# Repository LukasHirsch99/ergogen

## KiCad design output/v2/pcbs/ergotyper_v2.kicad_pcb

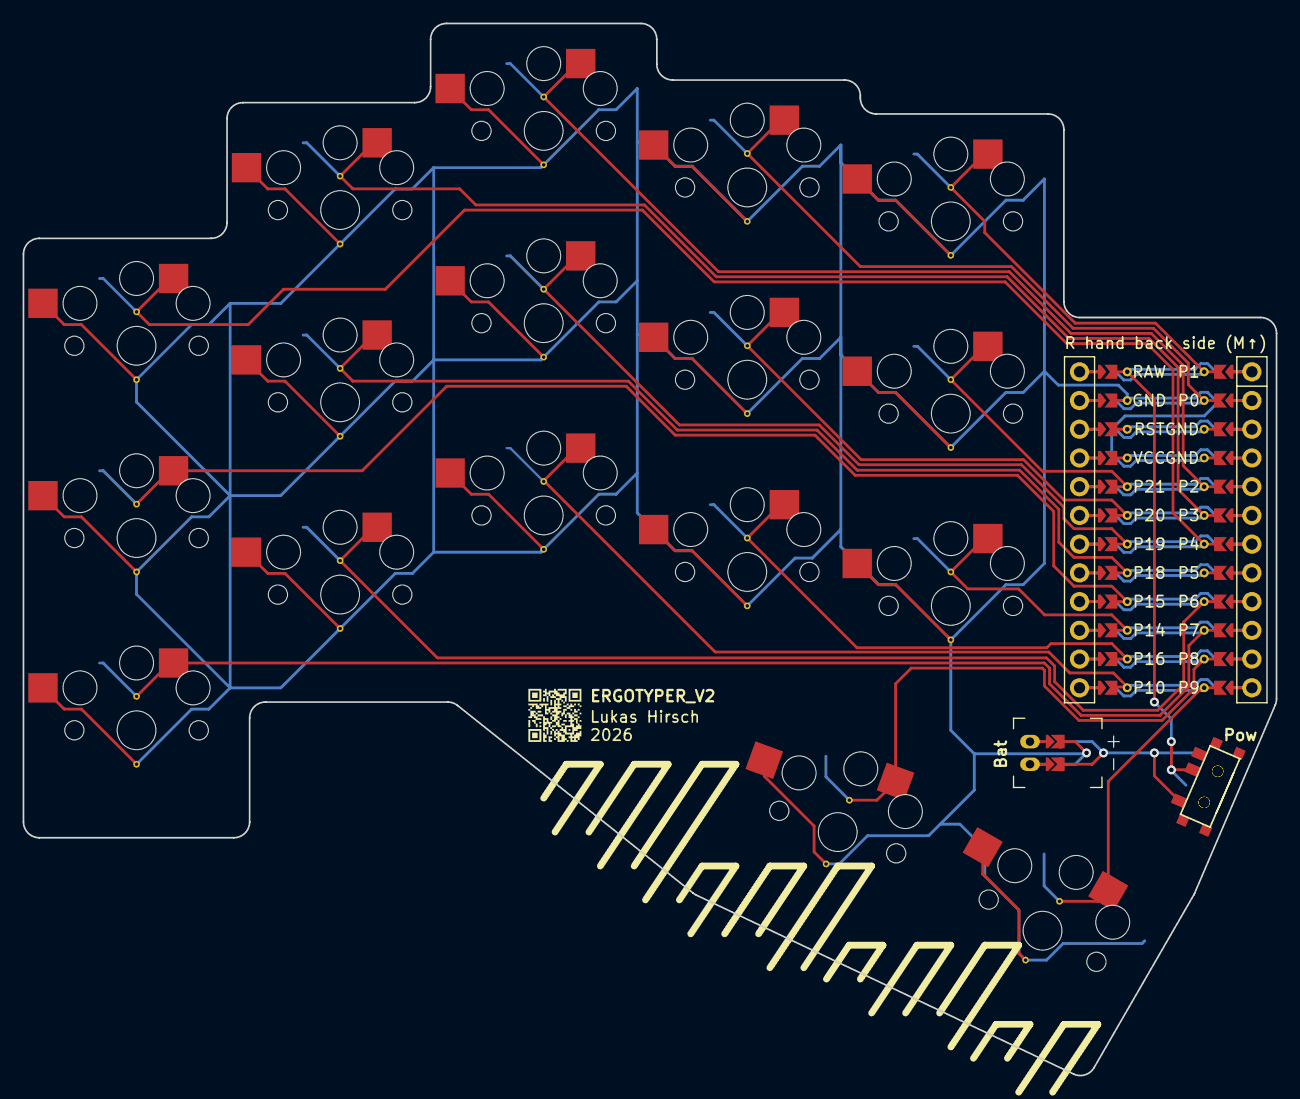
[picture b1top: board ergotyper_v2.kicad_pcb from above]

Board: 2 copper layers, 110.8 x 93.0 mm, 21 parts (0 on the bottom side), 22 nets.

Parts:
JST1: battery_connector_jst_ph_2
MCU1: mcu_nice_nano
S1, S2, S3, S4, S5, S6, S7, S8, S9, S10, S11, S12, S13, S14, S15, S16, S17: PG1350
T1, T2: SPDT_C128955

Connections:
BAT_P: JST1.1, T1.1, T2.1
GND: JST1.2, MCU1.103, MCU1.104, MCU1.123, S1.2, S2.2, S3.2, S4.2, S5.2, S6.2, S7.2, S8.2, S9.2, S10.2, S11.2, S12.2, S13.2, S14.2, S15.2, S16.2, S17.2
JST1_1: JST1.11, JST1.21, JST1.31
JST1_2: JST1.12, JST1.22, JST1.32
P0: MCU1.102, S12.1
P1: MCU1.101, S15.1
P2: MCU1.105, S9.1
P3: MCU1.106, S6.1
P4: MCU1.107, S3.1
P6: MCU1.109, S4.1
P7: MCU1.110, S1.1
P8: MCU1.111, S16.1
P9: MCU1.112, S17.1
P10: MCU1.113, S7.1
P14: MCU1.115, S13.1
P15: MCU1.116, S2.1
P16: MCU1.114, S10.1
P18: MCU1.117, S5.1
P19: MCU1.118, S8.1
P20: MCU1.119, S11.1
P21: MCU1.120, S14.1
RAW: MCU1.124, T1.2, T2.2

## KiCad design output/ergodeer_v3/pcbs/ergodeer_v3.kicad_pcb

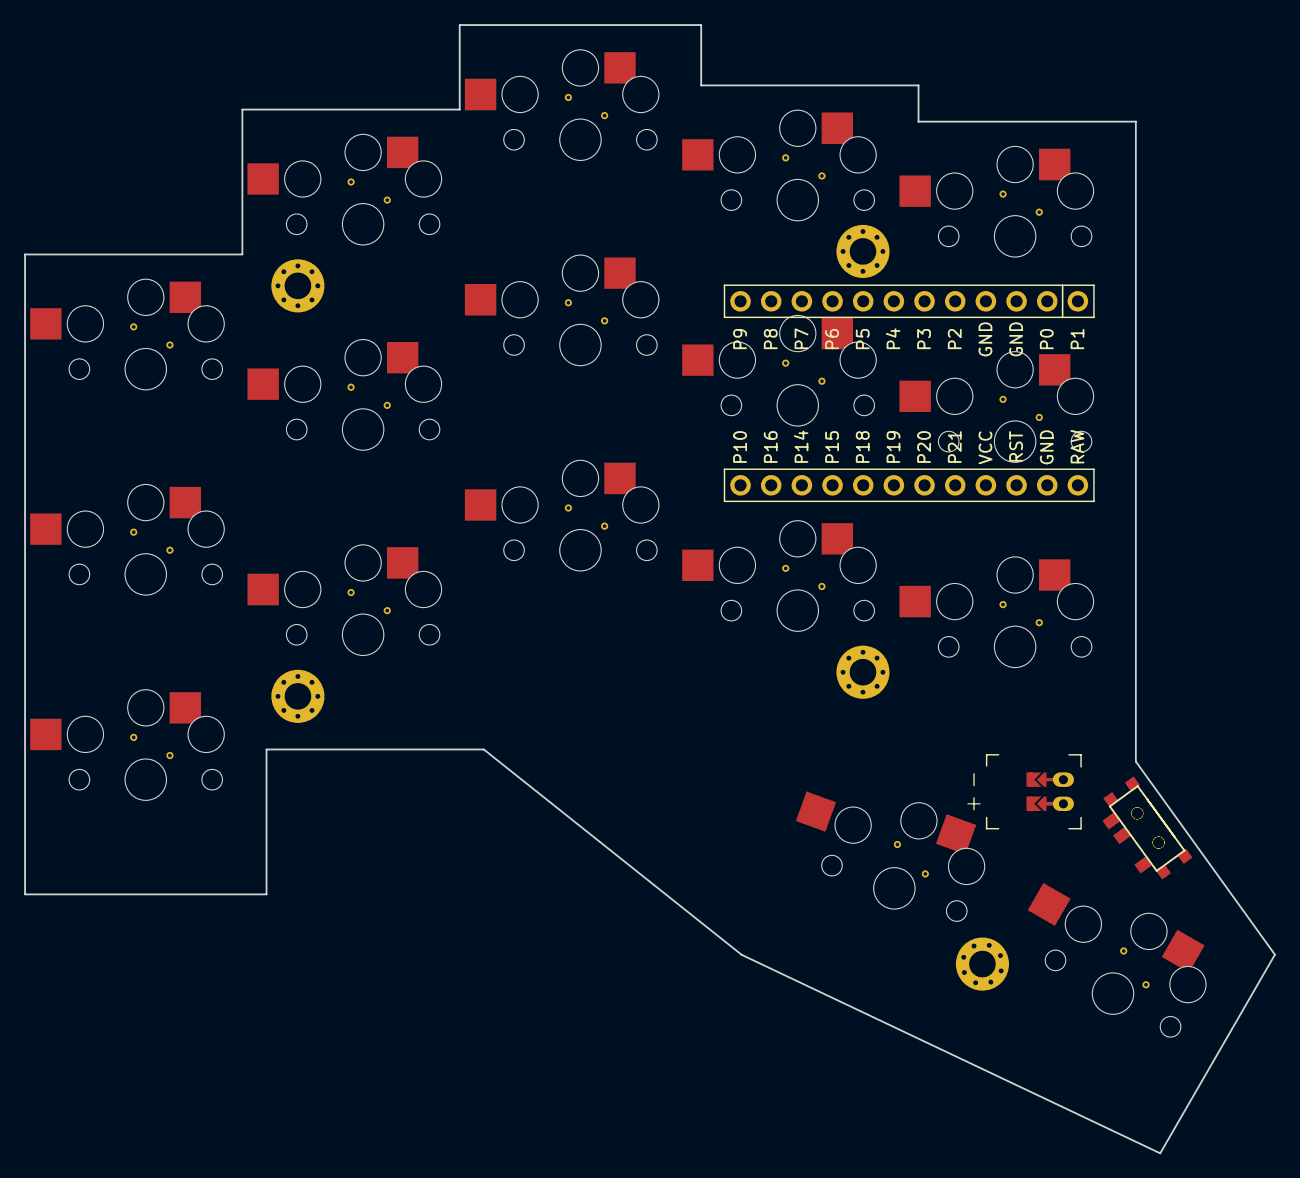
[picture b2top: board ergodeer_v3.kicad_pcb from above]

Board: 2 copper layers, 103.5 x 93.4 mm, 26 parts (0 on the bottom side), 22 nets.

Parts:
JST1: battery_connector_jst_ph_2
MCU1: mcu_nice_nano
S1, S2, S3, S4, S5, S6, S7, S8, S9, S10, S11, S12, S13, S14, S15, S16, S17: PG1350
T1, T2: SPDT_C128955
_35, _36, _37, _38, _39: MountingHole_2.2mm_M2_Pad_Via

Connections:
BAT_P: JST1.1, T1.1, T2.1
GND: JST1.2, MCU1.2, MCU1.21, MCU1.22, S1.2, S2.2, S3.2, S4.2, S5.2, S6.2, S7.2, S8.2, S9.2, S10.2, S11.2, S12.2, S13.2, S14.2, S15.2, S16.2, S17.2
JST1_1: JST1.11, JST1.21, JST1.31
JST1_2: JST1.12, JST1.22, JST1.32
P0: MCU1.23, S14.1
P1: MCU1.24, S15.1
P2: MCU1.20, S12.1
P3: MCU1.19, S9.1
P4: MCU1.18, S6.1
P5: MCU1.17, S3.1
P6: MCU1.16, S11.1
P7: MCU1.15, S8.1
P8: MCU1.14, S5.1
P10: MCU1.12, S7.1
P14: MCU1.10, S4.1
P15: MCU1.9, S1.1
P16: MCU1.11, S2.1
P18: MCU1.8, S10.1
P19: MCU1.7, S16.1
P20: MCU1.6, S17.1
P21: MCU1.5, S13.1
RAW: MCU1.1, T1.2, T2.2

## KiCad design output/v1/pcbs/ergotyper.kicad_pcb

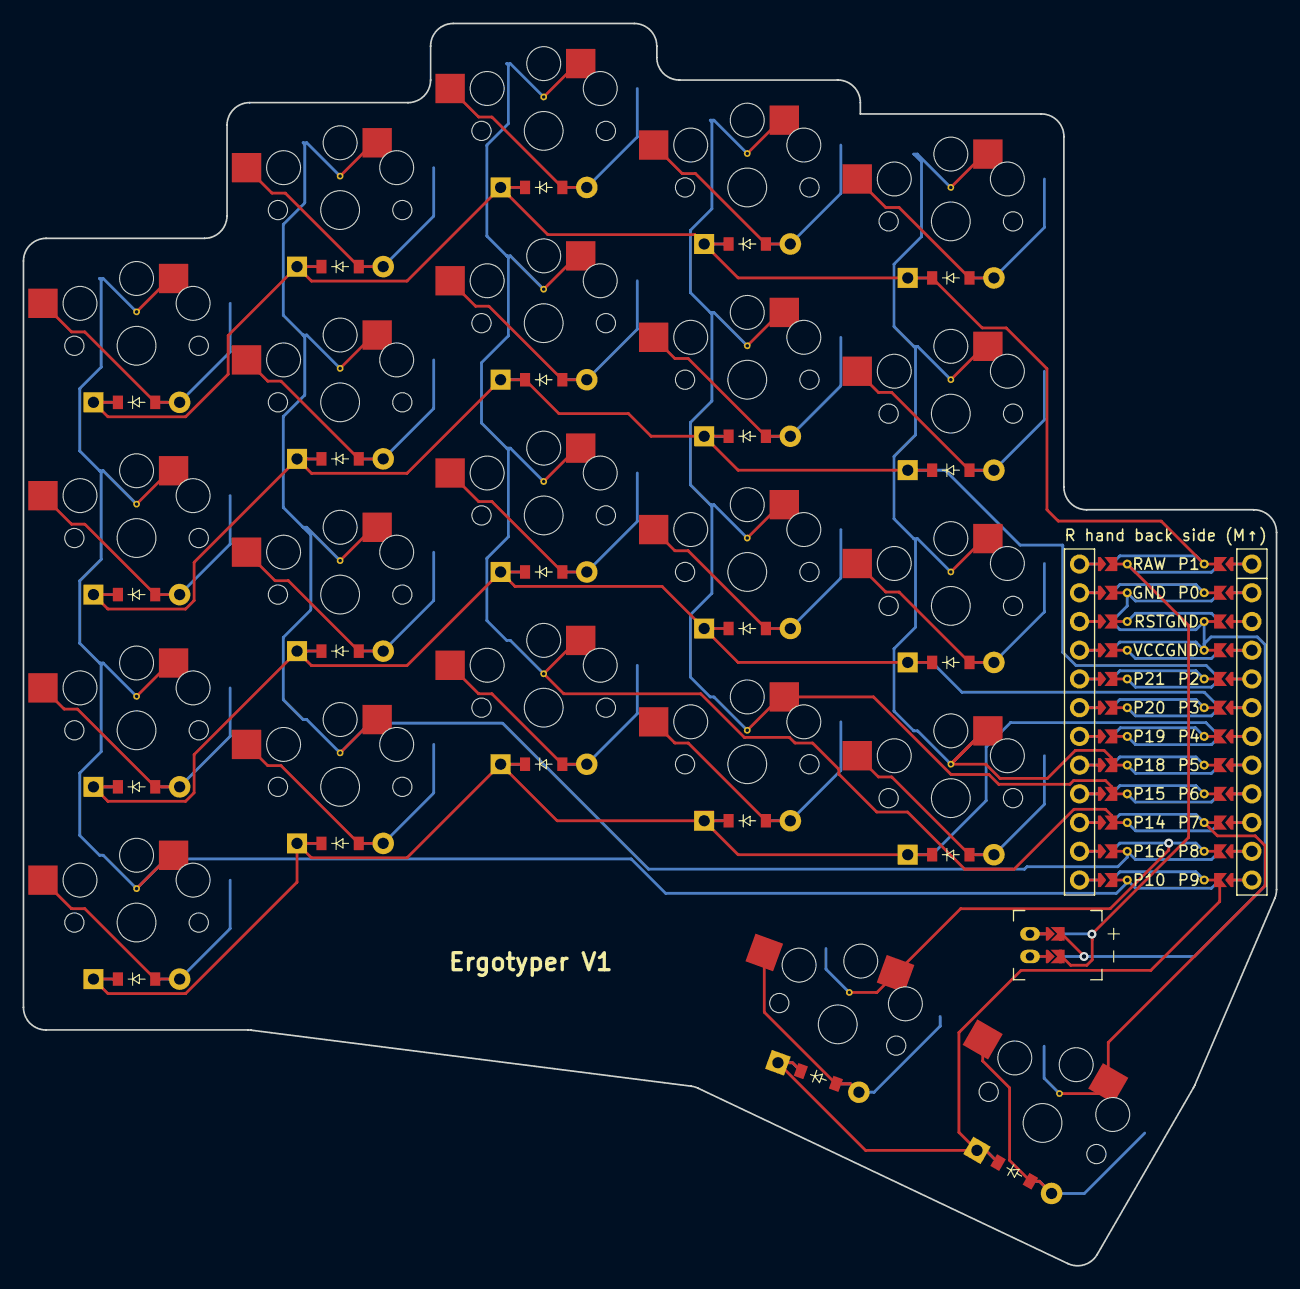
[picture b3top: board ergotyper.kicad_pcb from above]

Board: 2 copper layers, 110.8 x 109.8 mm, 46 parts (0 on the bottom side), 38 nets.

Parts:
D1, D2, D3, D4, D5, D6, D7, D8, D9, D10, D11, D12, D13, D14, D15, D16, D17, D18, D19, D20, D21, D22: ComboDiode
JST1: battery_connector_jst_ph_2
MCU1: mcu_nice_nano
S1, S2, S3, S4, S5, S6, S7, S8, S9, S10, S11, S12, S13, S14, S15, S16, S17, S18, S19, S20, S21, S22: PG1350

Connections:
GND: JST1.2, MCU1.103, MCU1.104, MCU1.123
JST1_1: JST1.11, JST1.21, JST1.31
JST1_2: JST1.12, JST1.22, JST1.32
P1: D4.1, D8.1, D12.1, D16.1, D20.1, MCU1.101
P7: MCU1.110, S22.1
P8: MCU1.111, S21.1
P9: D21.1, D22.1, MCU1.112
P10: MCU1.113, S1.1, S2.1, S3.1, S4.1
P14: MCU1.115, S9.1, S10.1, S11.1, S12.1
P15: MCU1.116, S13.1, S14.1, S15.1, S16.1
P16: MCU1.114, S5.1, S6.1, S7.1, S8.1
P18: MCU1.117, S17.1, S18.1, S19.1, S20.1
P19: D1.1, D5.1, D9.1, D13.1, D17.1, MCU1.118
P20: D2.1, D6.1, D10.1, D14.1, D18.1, MCU1.119
P21: D3.1, D7.1, D11.1, D15.1, D19.1, MCU1.120
RAW: JST1.1, MCU1.124
far_bottom: D17.2, S17.2
far_home: D18.2, S18.2
far_num: D20.2, S20.2
far_top: D19.2, S19.2
index_bottom: D13.2, S13.2
index_home: D14.2, S14.2
index_num: D16.2, S16.2
index_top: D15.2, S15.2
inner_cluster: D21.2, S21.2
middle_bottom: D9.2, S9.2
middle_home: D10.2, S10.2
middle_num: D12.2, S12.2
middle_top: D11.2, S11.2
outer_cluster: D22.2, S22.2
pinkie_bottom: D1.2, S1.2
pinkie_home: D2.2, S2.2
pinkie_num: D4.2, S4.2
pinkie_top: D3.2, S3.2
ring_bottom: D5.2, S5.2
ring_home: D6.2, S6.2
ring_num: D8.2, S8.2
ring_top: D7.2, S7.2

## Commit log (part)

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2026-02-01 Add v1
